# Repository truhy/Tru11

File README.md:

Tru11
-----

A command line program for reading and writing Motorola 68HC11 series microcontroller (MCU).

Example devices:
MC68HC11E1
MC68HC11E9
MC68HC711E9
MC68HC11E20
MC68HC711E20
MC68HC811E2

The MCU must start in the bootstrap mode with an 8MHz crystal.
The mode can be selected by connecting MODA + MODB pins to ground.

In bootstrap mode, the built-in bootloader program in the ROM will execute, which then waits for the host to send it a user program to place into RAM, and then executes it by jumping to RAM address 0x0000.

This command line program requires the tru11 talker program (talker firmware) to be downloaded into the MCU RAM first.

TBug11
------

This is an alternative program to Tru11, which achieves the same thing but uses JBug11 talker firmware (by John Beatty) instead.
The original JBug11 firmware is interrupt driven, and this requires the XIRQ or IRQ pins to be pulled up to VDD (5V supply).  But on my minimal programming board, these are floating and so will not work.
I've modified the firmware, adding in a new option (made default) for a polling method, which enables the minimal programming board to work.

68HC11 programming board
------------------------

The schematics folder contains KiCad EDA files for a minimal and standard programming board with a PLCC52 socket.

The minimal version is enough for reading (all) and writing registers, RAM, EEPROM, but not EPROM.

The standard includes:
- DIP switches for boot mode options
- 12V input to support writing EPROM
- Reset button

On both versions, there is a header with 5V input supply and 5V TTL serial pins, which you can wire directly to a serial TTL-to-USB adapter, e.g. CH340 (plenty on ebay) or FT232 ready made board, please set the jumper to 5V if the board has the option.

Example run scripts
-------------------

The example run scripts make use of the settings in the script:
- env_win.bat (if using Windows)
- env_linux.sh (if using Linux)

Edit the script with the correct serial port path, then run:
- upload_talker.bat (if using Windows)
- upload_talker.sh (if using Linux)

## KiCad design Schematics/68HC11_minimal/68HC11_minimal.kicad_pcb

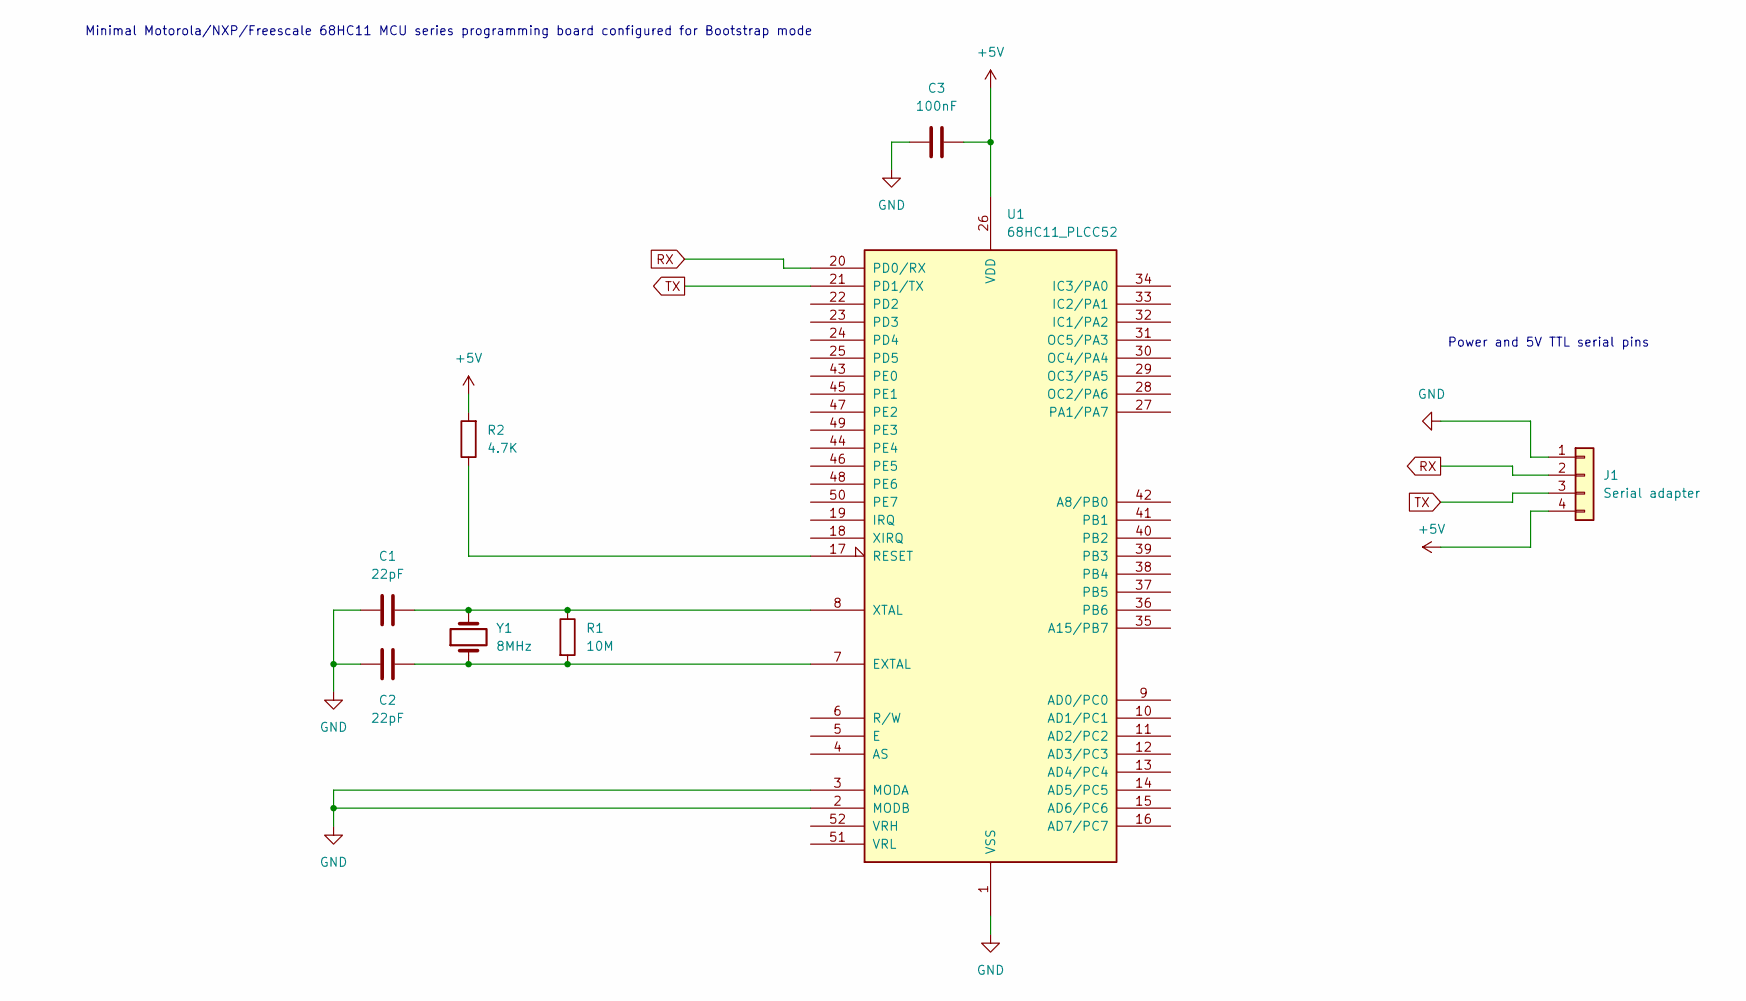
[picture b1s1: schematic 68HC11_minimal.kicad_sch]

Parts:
C1, C2: 22pF; C_0805_2012Metric_Pad1.18x1.45mm_HandSolder
C3: 100nF; C_0805_2012Metric_Pad1.18x1.45mm_HandSolder
J1: Serial adapter; PinHeader_1x04_P2.54mm_Vertical
R1: 10M; R_0805_2012Metric_Pad1.20x1.40mm_HandSolder
R2: 4.7K; R_0805_2012Metric_Pad1.20x1.40mm_HandSolder
U1: 68HC11_PLCC52; PLCC-52_THT-Socket
Y1: 8MHz; Crystal_HC49-4H_Vertical

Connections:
+5V: C3.2, J1.4, R2.2, U1.26 (VDD)
GND: C1.1, C2.1, C3.1, J1.1, U1.1 (VSS), U1.2 (MODB), U1.3 (MODA)
unnamed: C2.2, R1.2, U1.7 (EXTAL), Y1.1
unnamed: R2.1, U1.17 (RESET)
unnamed: C1.2, R1.1, U1.8 (XTAL), Y1.2
RX: J1.2, U1.20 (PD0/RX)
TX: J1.3, U1.21 (PD1/TX)

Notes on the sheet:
Power and 5V TTL serial pins
Minimal Motorola/NXP/Freescale 68HC11 MCU series programming board configured for Bootstrap mode

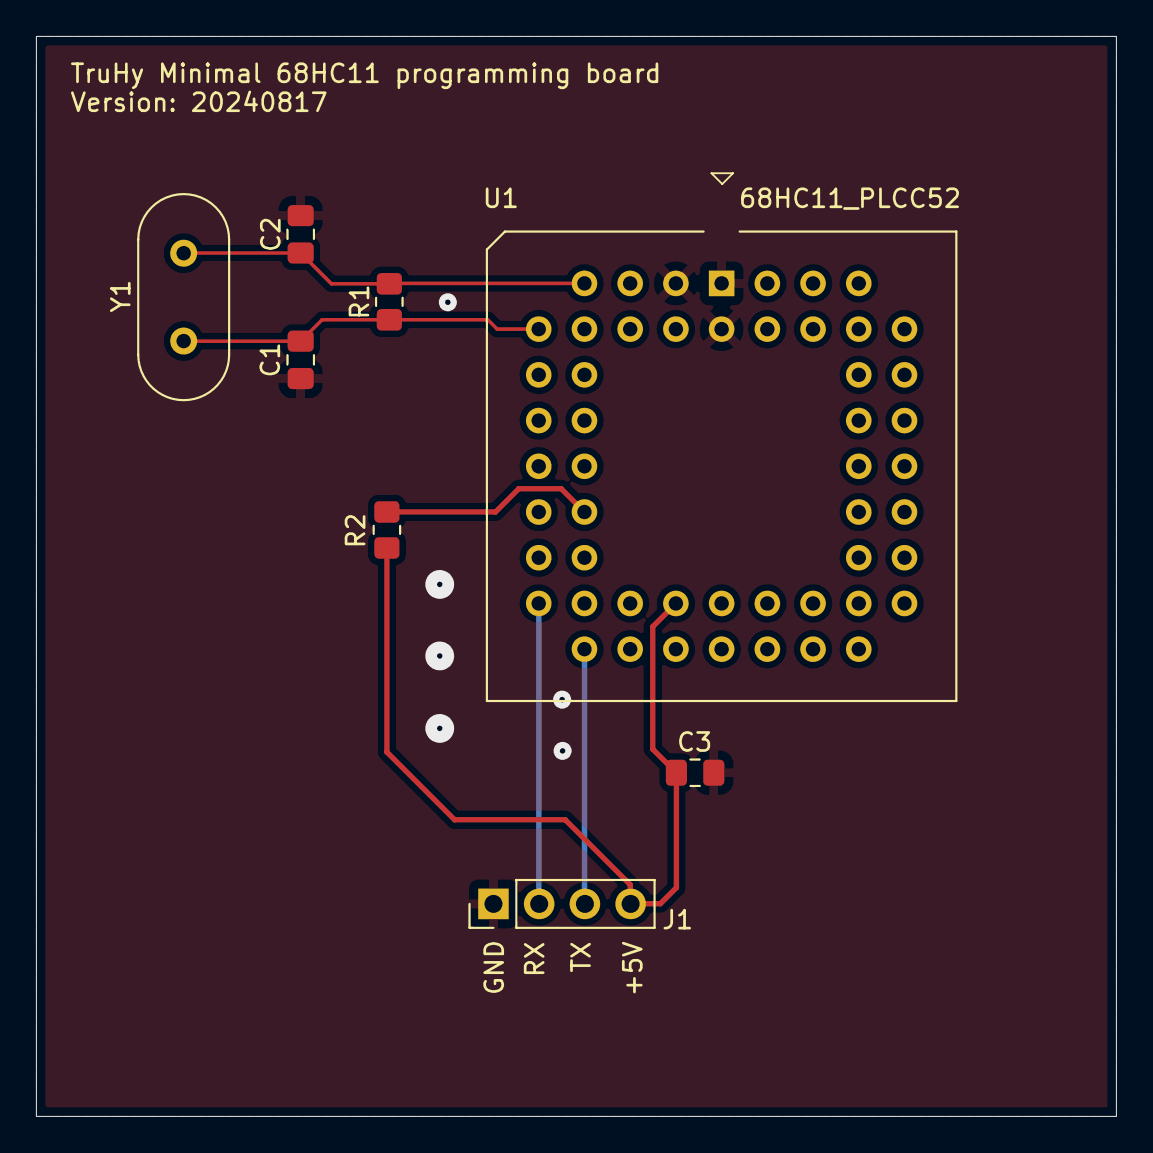
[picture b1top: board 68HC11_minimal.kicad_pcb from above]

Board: 2 copper layers, 60.0 x 60.0 mm, 8 parts (0 on the bottom side), 7 nets.

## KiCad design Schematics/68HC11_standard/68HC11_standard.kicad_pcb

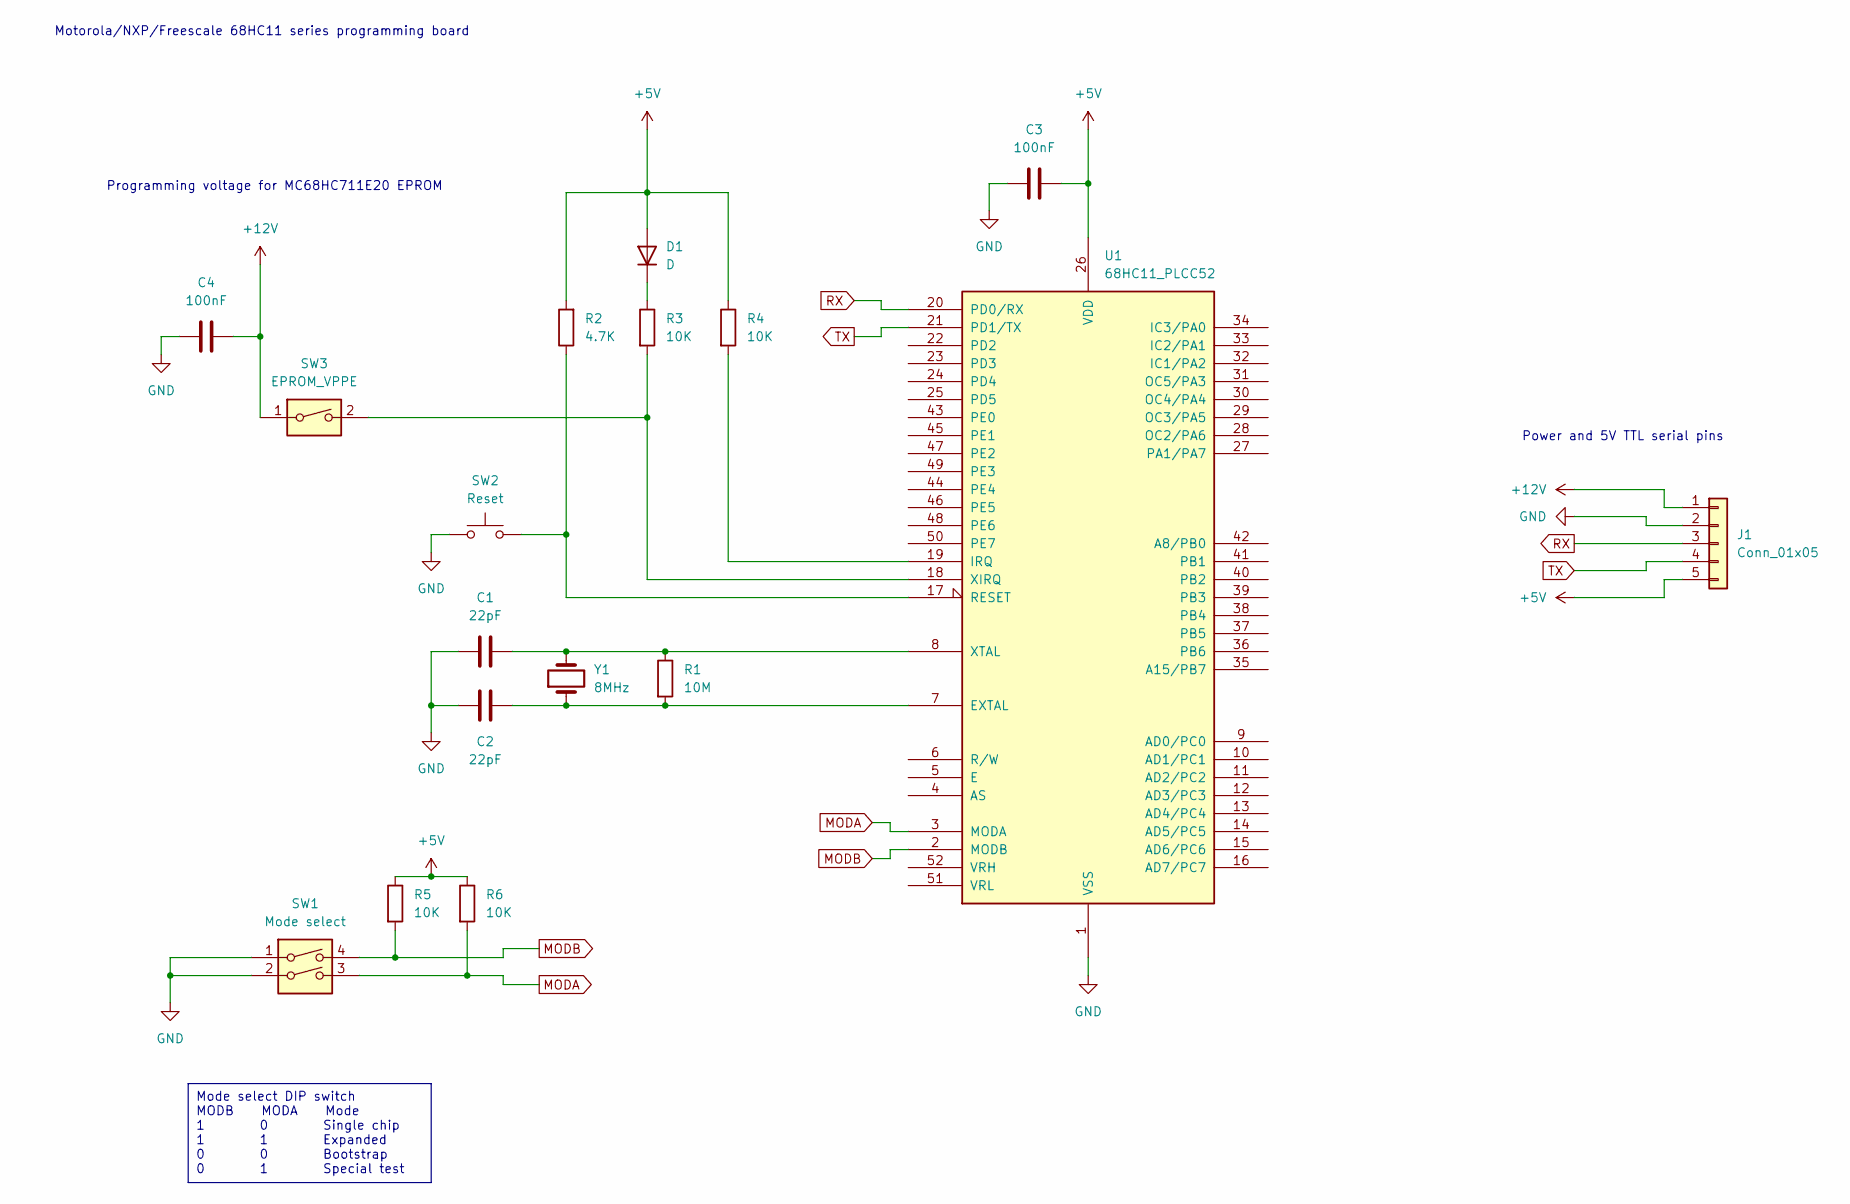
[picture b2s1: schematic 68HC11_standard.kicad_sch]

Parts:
C1, C2: 22pF; C_0805_2012Metric_Pad1.18x1.45mm_HandSolder
C3, C4: 100nF; C_0805_2012Metric_Pad1.18x1.45mm_HandSolder
D1: D
J1: Conn_01x05; PinHeader_1x05_P2.54mm_Vertical
R1: 10M; R_0805_2012Metric_Pad1.20x1.40mm_HandSolder
R2: 4.7K; R_0805_2012Metric_Pad1.20x1.40mm_HandSolder
R3, R4, R5, R6: 10K; R_0805_2012Metric_Pad1.20x1.40mm_HandSolder
SW1: Mode select; SW_DIP_SPSTx02_Slide_9.78x7.26mm_W7.62mm_P2.54mm
SW2: Reset; SW_SPST_Omron_B3FS-100xP
SW3: EPROM_VPPE; SW_DIP_SPSTx01_Slide_9.78x4.72mm_W7.62mm_P2.54mm
U1: 68HC11_PLCC52; PLCC-52_THT-Socket
Y1: 8MHz; Crystal_HC49-4H_Vertical

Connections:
+5V: C3.2, D1.1 (K), D1.2 (A), J1.5, R2.2, R3.1, R4.1, R5.1, R6.1, U1.26 (VDD)
+12V: C4.2, J1.1, SW3.1
GND: C1.1, C2.1, C3.1, C4.1, J1.2, SW1.1, SW1.2, SW2.1, U1.1 (VSS)
MODA: R6.2, SW1.3, U1.3 (MODA)
MODB: R5.2, SW1.4, U1.2 (MODB)
unnamed: C2.2, R1.2, U1.7 (EXTAL), Y1.1
unnamed: R4.2, U1.19 (IRQ)
unnamed: R2.1, SW2.2, U1.17 (RESET)
unnamed: R3.2, SW3.2, U1.18 (XIRQ)
unnamed: C1.2, R1.1, U1.8 (XTAL), Y1.2
RX: J1.3, U1.20 (PD0/RX)
TX: J1.4, U1.21 (PD1/TX)

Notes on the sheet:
Mode select DIP switch MODB MODA Mode 1 0 Single chip 1 1 Expanded 0 0 Bootstrap 0 1 Special test
Power and 5V TTL serial pins
Programming voltage for MC68HC711E20 EPROM
Motorola/NXP/Freescale 68HC11 series programming board

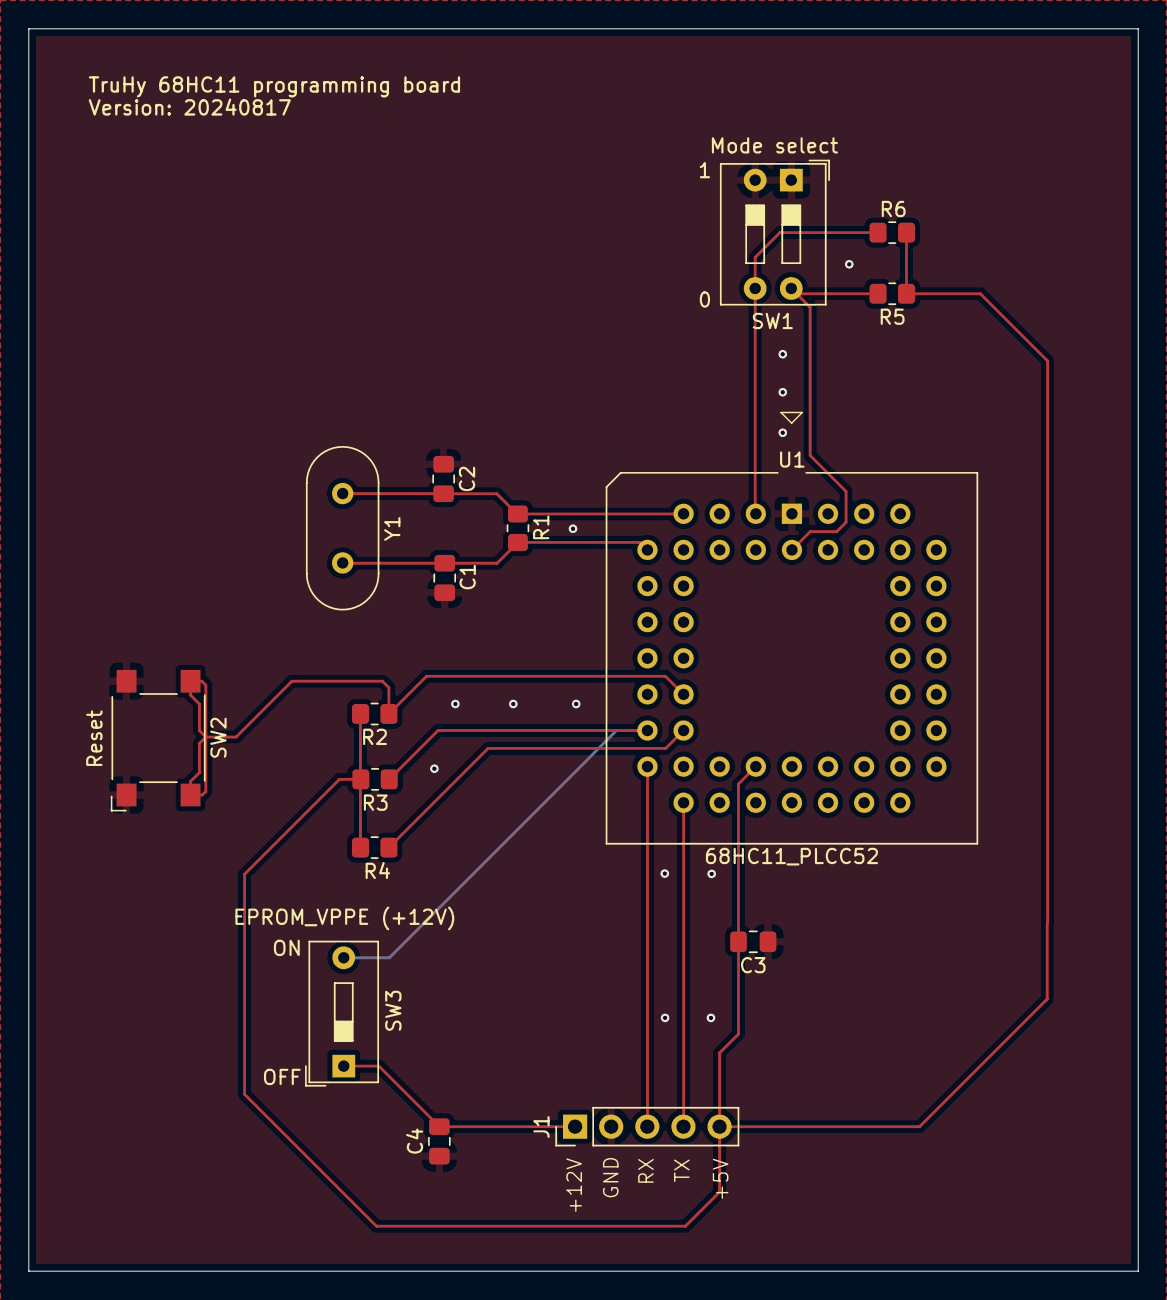
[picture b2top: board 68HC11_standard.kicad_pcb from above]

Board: 2 copper layers, 78.0 x 87.4 mm, 16 parts (0 on the bottom side), 12 nets.

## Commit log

2024-09-23 Update JBug_Talk.asm
    Idle loop (do nothing until an interrupt) was commented out for debugging. Re-enabled it according to the IntType.
2024-11-24 Corrected the handle name
    corrected the handle name to fd
2025-04-11 Changed object folder paths
